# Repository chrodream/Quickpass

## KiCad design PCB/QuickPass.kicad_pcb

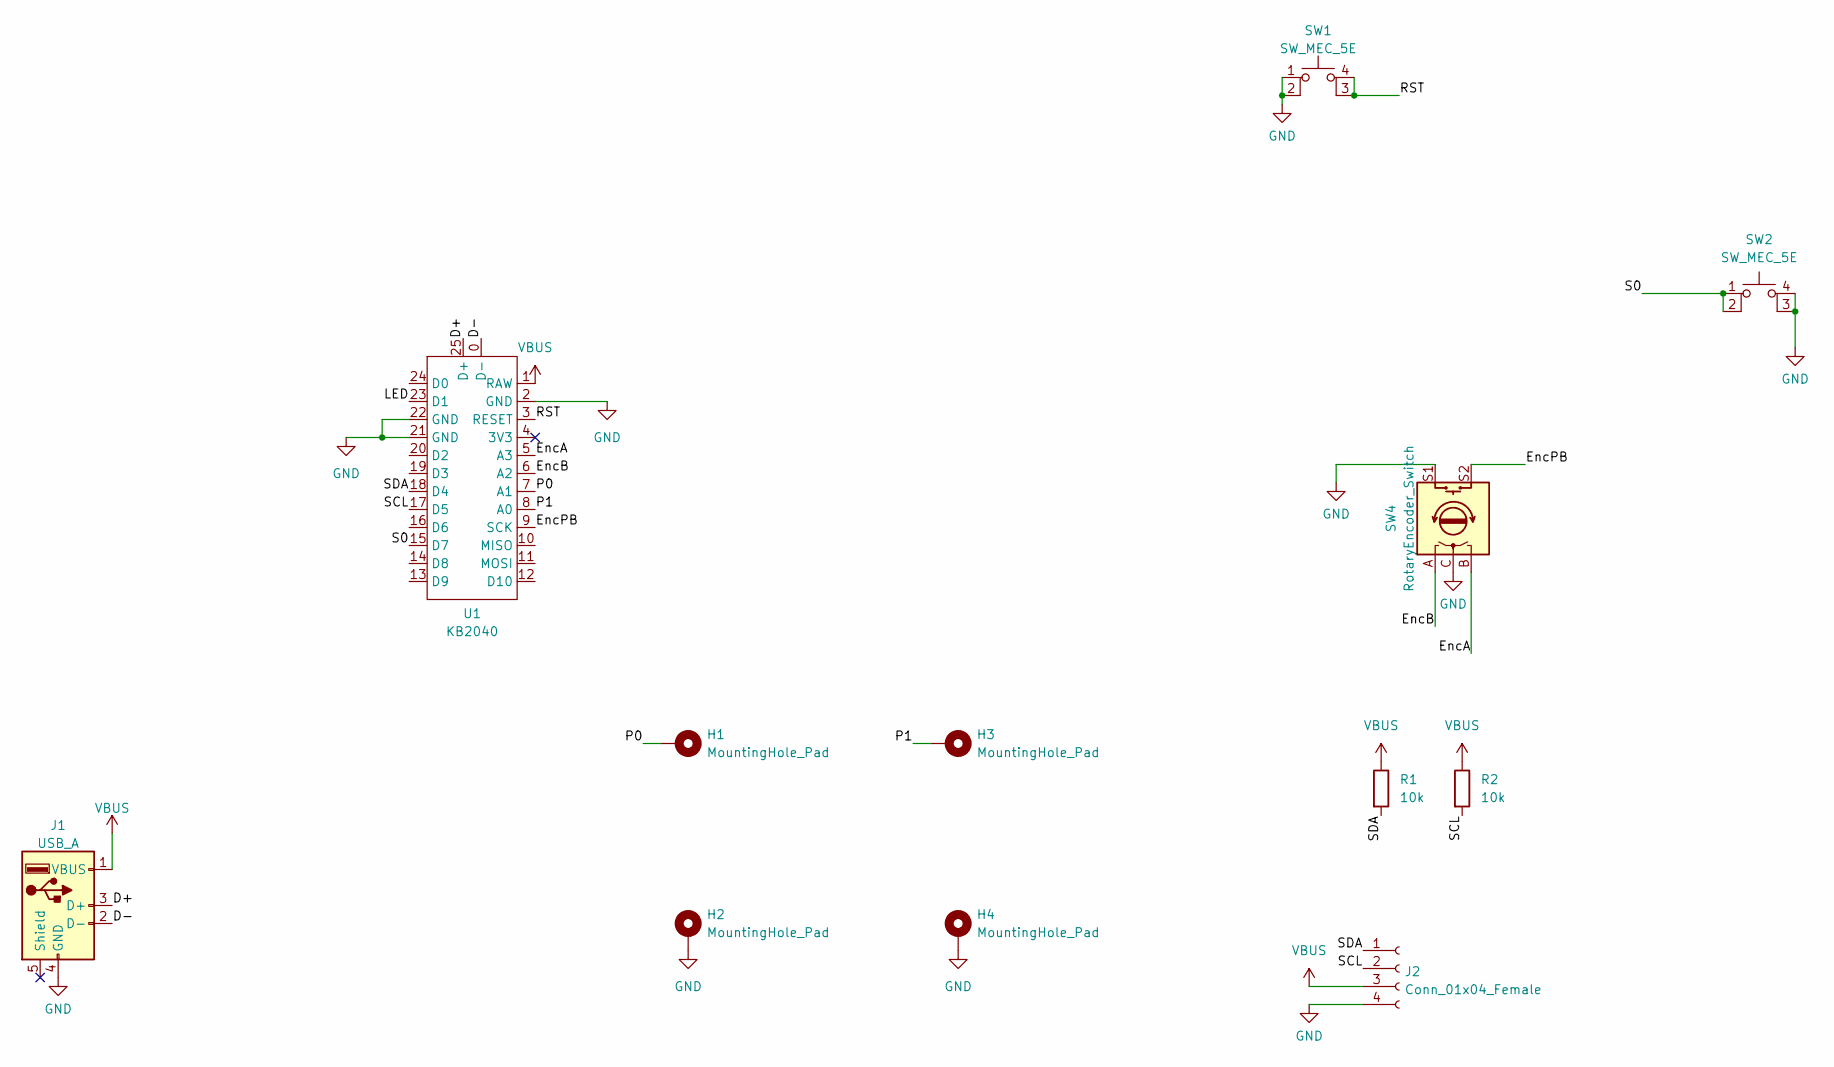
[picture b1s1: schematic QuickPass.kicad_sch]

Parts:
H1, H2, H3, H4: MountingHole_Pad; MountingHole_2.2mm_M2_DIN965_Pad
J1: USB_A; USB-4AM103
J2: Conn_01x04_Female; PinSocket_1x04_P2.54mm_Vertical
R1, R2: 10k; R_0603_1608Metric
SW1, SW2: SW_MEC_5E; THAU13-AB-R
SW4: RotaryEncoder_Switch; RotaryEncoder_Alps_EC12E-Switch_Vertical_H20mm_CircularMoun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
U1: KB2040

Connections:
/D+: J1.3 (D+), U1.25 (D+)
/D-: J1.2 (D-), U1.0 (D-)
/EncA: SW4.B, U1.5 (A3)
/EncB: SW4.A, U1.6 (A2)
/EncPB: SW4.S2, U1.9 (SCK)
/LED: U1.23 (D1)
/P0: H1.1, U1.7 (A1)
/P1: H3.1, U1.8 (A0)
/RST: SW1.3 (K), SW1.4 (A), U1.3 (RESET)
/S0: SW2.1, SW2.2, U1.15 (D7)
/SCL: J2.2, R2.2, U1.17 (D5)
/SDA: J2.1, R1.2, U1.18 (D4)
GND: H2.1, H4.1, J1.4 (GND), J2.4, SW1.1, SW1.2, SW2.3 (K), SW2.4 (A), SW4.C, SW4.S1, U1.2 (GND), U1.21 (GND), U1.22 (GND)
VBUS: J1.1 (VBUS), J2.3, R1.1, R2.1, U1.1 (RAW)

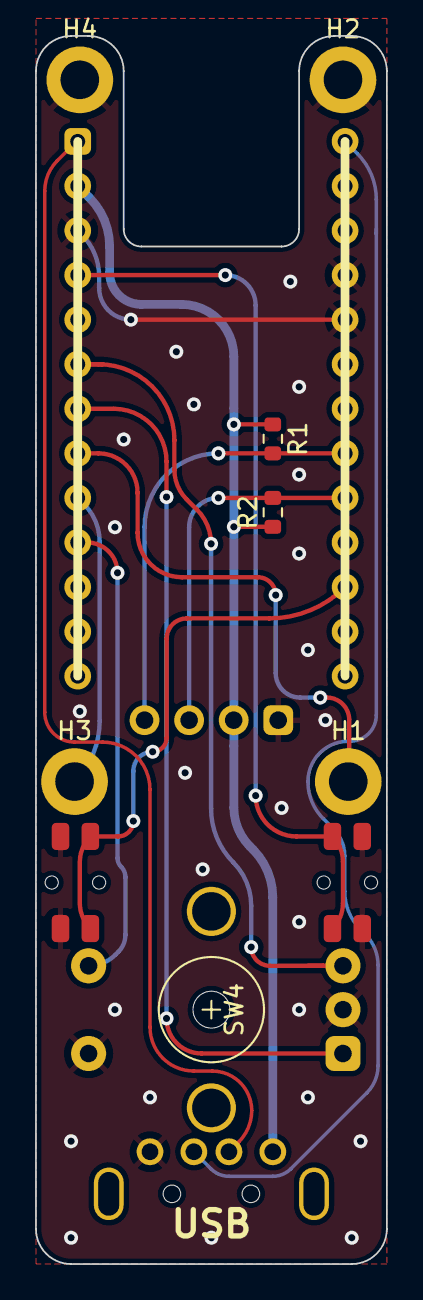
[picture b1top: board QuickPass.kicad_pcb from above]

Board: 2 copper layers, 20.0 x 70.0 mm, 12 parts (0 on the bottom side), 13 nets.

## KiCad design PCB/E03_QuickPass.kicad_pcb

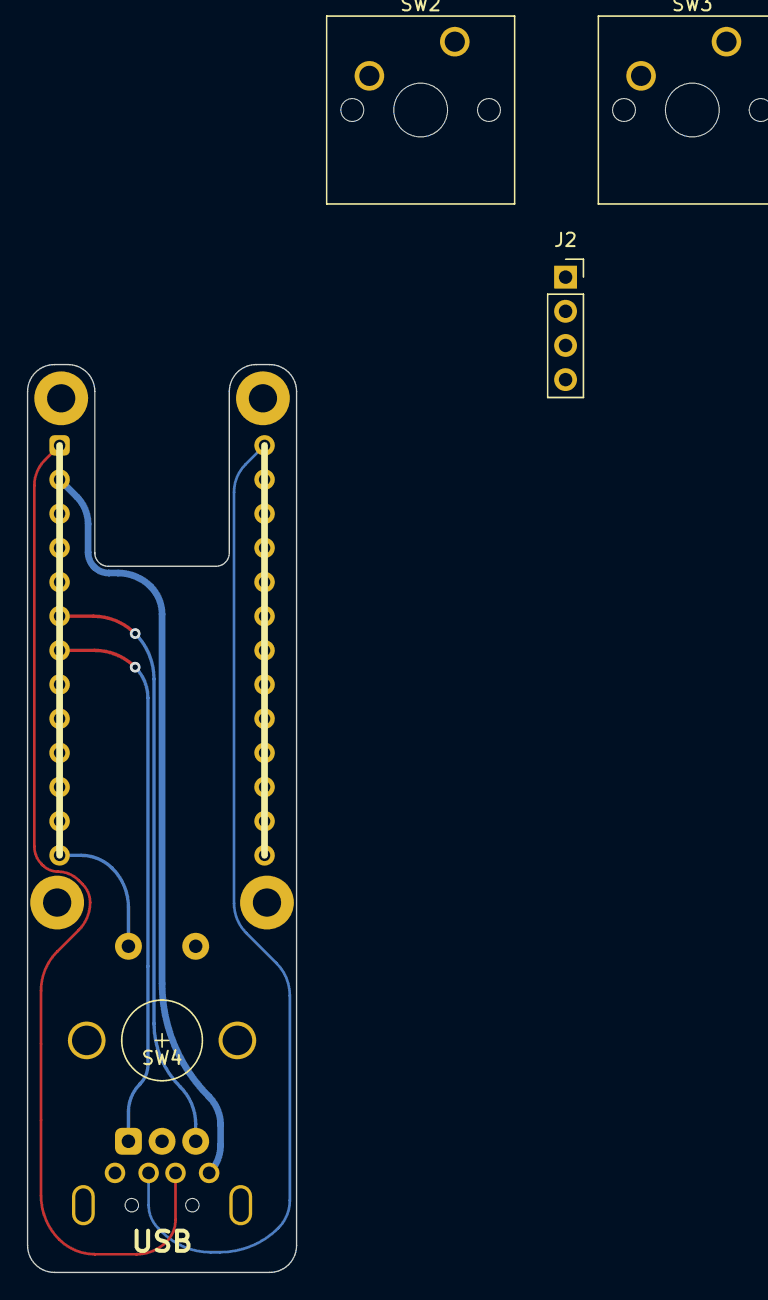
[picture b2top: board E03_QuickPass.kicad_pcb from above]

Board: 2 copper layers, 20.0 x 67.5 mm, 6 parts (0 on the bottom side), 11 nets.

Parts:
J1: USB_A; USB-4AM103
J2: Conn_01x04_Female; PinSocket_1x04_P2.54mm_Vertical
SW2, SW3: SW_Push; SW_Cherry_MX_1.00u_PCB
SW4: RotaryEncoder_Switch; RotaryEncoder_Alps_EC12E-Switch_Vertical_H20mm_CircularMoun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
U1: KB2040

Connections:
/D+: J1.3 (D+), U1.25 (D+)
/D-: J1.2 (D-), U1.0 (D-)
/EncA: SW4.B, U1.5 (A3)
/EncB: SW4.A, U1.6 (A2)
/EncPB: SW4.S1, U1.12 (D10)
/P0: SW2.1, U1.10 (MISO)
/P1: SW3.1, U1.11 (MOSI)
/SCL: J2.3, U1.19 (D3)
/SDA: J2.4, U1.20 (D2)
GND: J1.4 (GND), J2.1, SW2.2, SW3.2, SW4.C, SW4.S2, U1.2 (GND), U1.21 (GND), U1.22 (GND)
VBUS: J1.1 (VBUS), U1.1 (RAW)

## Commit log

2023-02-08 change pcb design and add code
2023-02-09 separate PCB switch and MCU
2023-02-19 add lower plate
